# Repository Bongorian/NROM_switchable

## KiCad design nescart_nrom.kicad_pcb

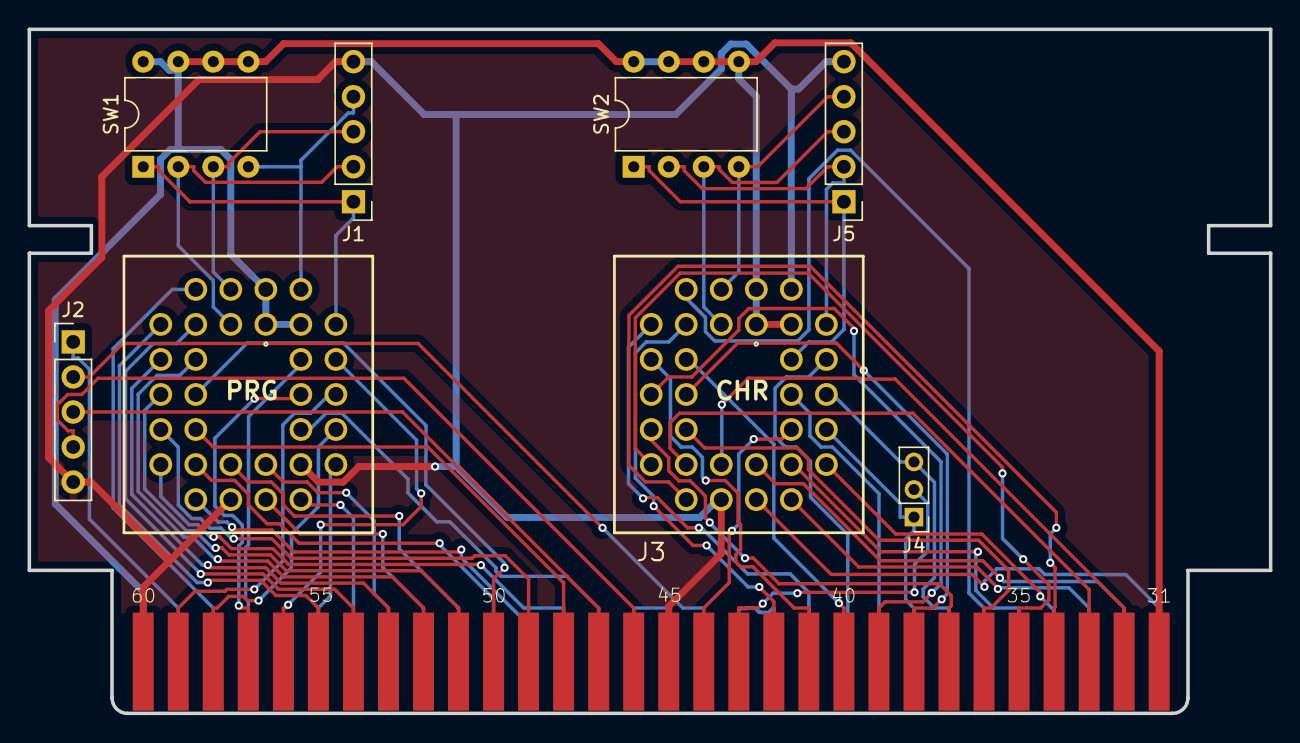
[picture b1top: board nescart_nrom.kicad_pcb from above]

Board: 2 copper layers, 90.0 x 49.6 mm, 9 parts (0 on the bottom side), 63 nets.

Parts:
CHR: CHR ROM; 540-88-032-24-008
J1, J5: SIP R; Pin_Header_Straight_1x05_Pitch2.54mm
J2: DEBUG; Pin_Header_Straight_1x05_Pitch2.54mm
J3: EDGE; FAMICOM
J4: H/V; Pin_Header_Straight_1x03_Pitch2.00mm
PRG: PRG ROM; 540-88-032-24-008
SW1, SW2: SW_DIP_x04; DIP-8_W7.62mm

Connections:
/PA13: J3.12, J3.13
A0: J3.48, PRG.12
A1: J3.49, PRG.11
A2: J3.50, PRG.10
A3: J3.51, PRG.9
A4: J3.52, PRG.8
A5: J3.53, PRG.7
A6: J3.54, PRG.6
A7: J3.55, PRG.5
A8: J3.56, PRG.27
A9: J3.57, PRG.26
A10: J3.58, PRG.23
A11: J3.59, PRG.25
A12: J3.28, PRG.4
A13: J3.27, PRG.28
D0: J3.18, PRG.13
D1: J3.19, PRG.14
D2: J3.20, PRG.15
D3: J3.21, PRG.17
D4: J3.22, PRG.18
D5: J3.23, PRG.19
D6: J3.24, PRG.20
D7: J3.25, PRG.21
F2: J2.1, J3.29
GND: CHR.16, CHR.30, J1.5, J2.5, J3.45, J3.60, J5.5, PRG.16, PRG.22
IN: J3.15, J3.16
IRQ: J2.4, J3.46
unnamed: J1.3, PRG.2, SW1.3
unnamed: J1.2, PRG.3, SW1.2
unnamed: J1.1, PRG.29, SW1.1
unnamed: J1.4, PRG.30, SW1.4
unnamed: CHR.2, J5.4, SW2.4
unnamed: CHR.3, J5.3, SW2.3
unnamed: CHR.28, J5.1, SW2.1
unnamed: CHR.29, J5.2, SW2.2
PA0: CHR.12, J3.36
PA1: CHR.11, J3.37
PA2: CHR.10, J3.38
PA3: CHR.9, J3.39
PA4: CHR.8, J3.40
PA5: CHR.7, J3.41
PA6: CHR.6, J3.42
PA7: CHR.5, J3.11
PA8: CHR.27, J3.10
PA9: CHR.26, J3.9
PA10: CHR.23, J3.8, J4.1
PA11: CHR.25, J3.7, J4.3
PA12: CHR.4, J3.6
PA13: CHR.22, J3.5
PD0: CHR.13, J3.35
PD1: CHR.14, J3.34
PD2: CHR.15, J3.33
PD3: CHR.17, J3.32
PD4: CHR.18, J3.1
PD5: CHR.19, J3.2
PD6: CHR.20, J3.3
PD7: CHR.21, J3.4
RD: CHR.24, J3.44
ROMSEL: J3.17, PRG.24
RW: J2.3, J3.47
VCC: CHR.1, CHR.31, CHR.32, J3.30, J3.31, PRG.1, PRG.31, PRG.32, SW1.5, SW1.6, SW1.7, SW1.8, SW2.5, SW2.6, SW2.7, SW2.8
VRAMA10: J3.43, J4.2
WE: J2.2, J3.14
